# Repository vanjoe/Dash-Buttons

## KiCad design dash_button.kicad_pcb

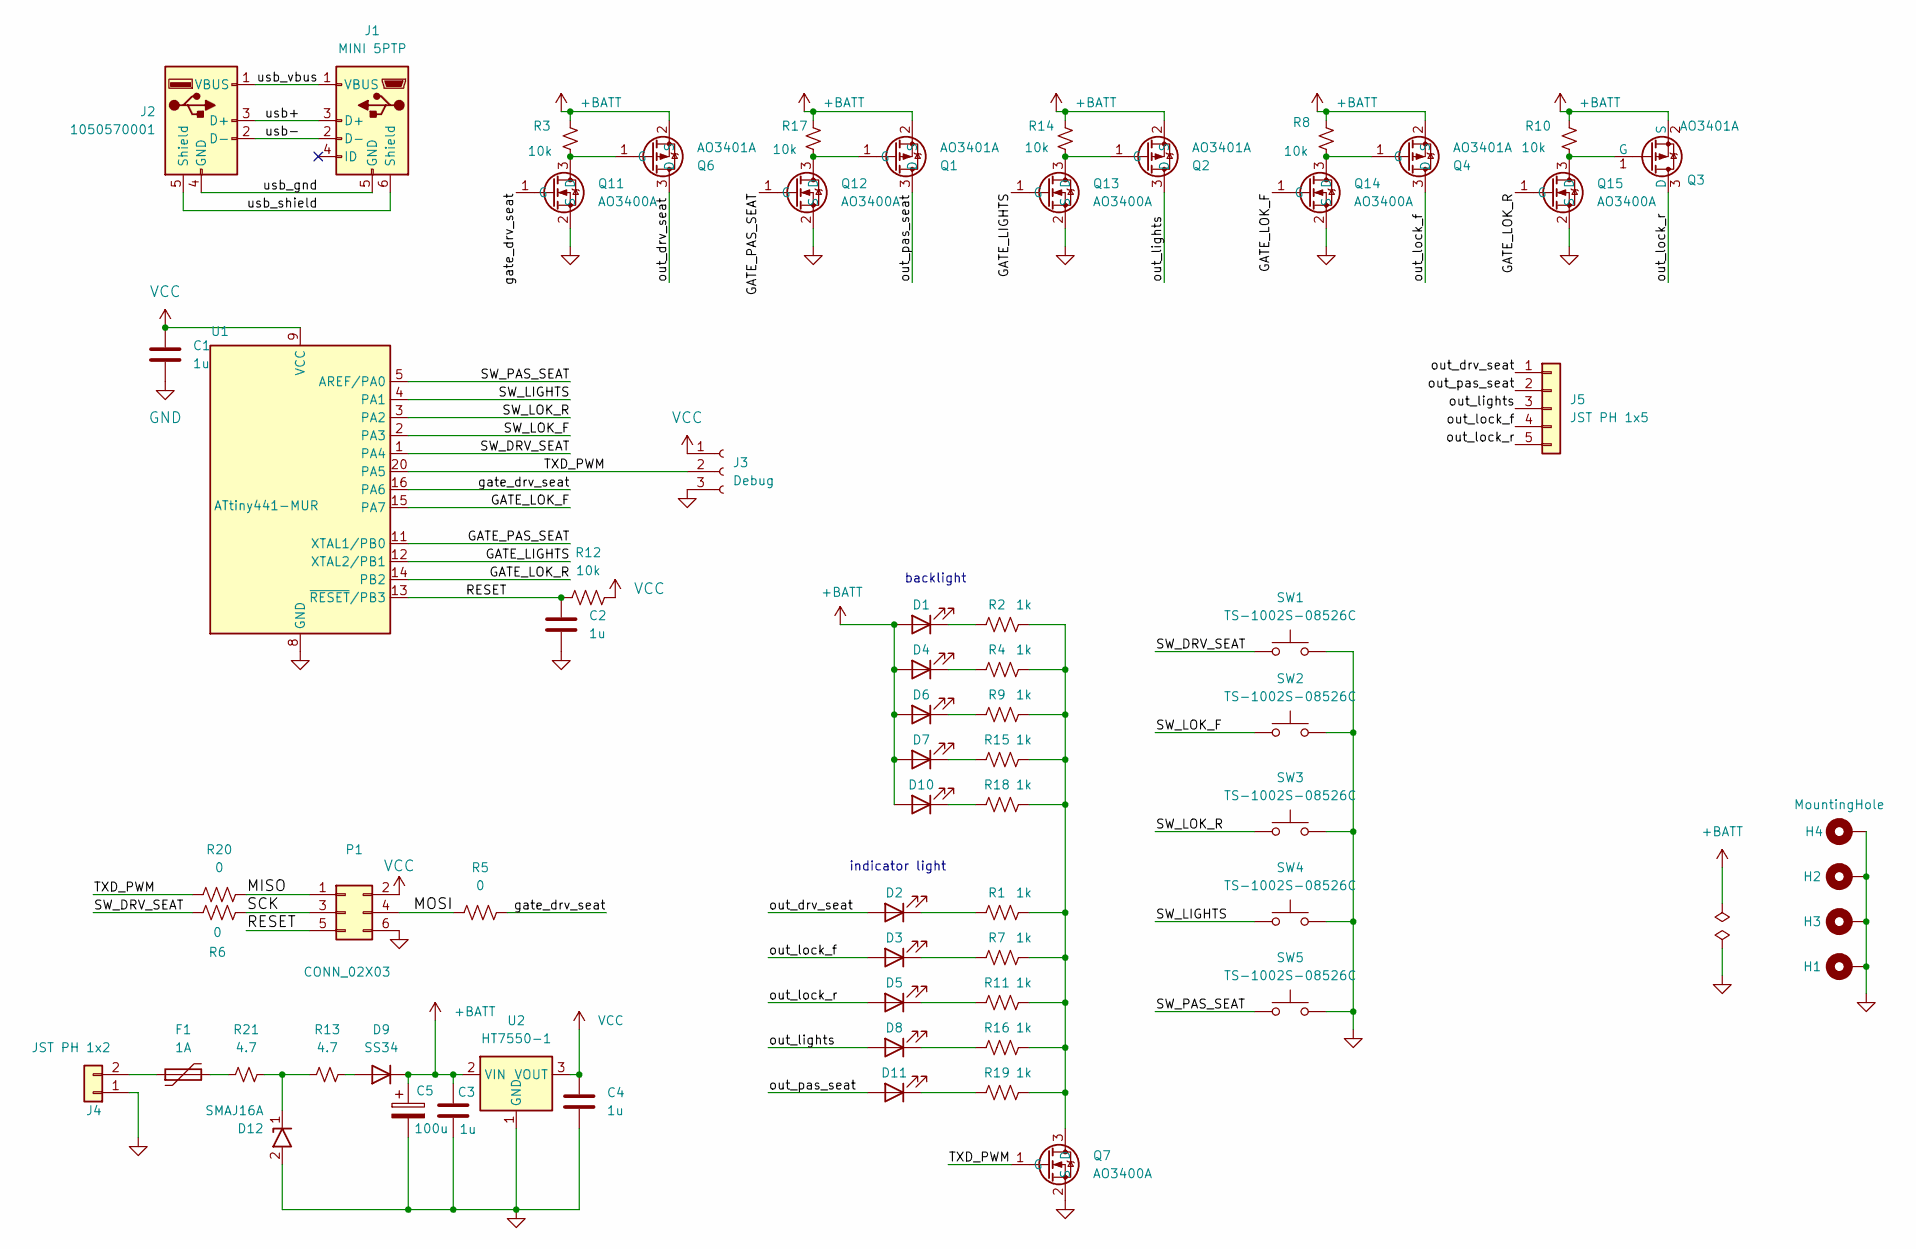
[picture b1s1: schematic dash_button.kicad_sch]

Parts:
C1, C2, C3, C4: 1u; C_0603_1608Metric; PartNo CL10A105KB8NNNC; LCSC Part # C15849
C5: 100u; CP_Elec_6.3x5.3; MPN VES101M1CTR-0605; LCSC Part # C176674
D1, D4, D6, D7, D10: KT-0805G; LED_0805_2012Metric; MPN KT-0805G; LCSC Part # C2297
D2, D3, D5, D8, D11: LED; LED_D3.0mm; MPN L314HD
D9: SS34; D_SMA; MPN SS34; LCSC Part # C8678
D12: SMAJ16A; D_SMA; MPN SMAJ16A; LCSC Part # C908770
F1: 1A; Fuse_1206_3216Metric; MPN BSMD1206-100-30V; LCSC Part # C5358568
H1, H2, H3, H4: MountingHole; MountingHole_3.2mm_M3_DIN965_Pad
J1: MINI 5PTP; USB_Mini-B_Wuerth_65100516121_Horizontal; MPN MINI 5PTP; LCSC Part # C2681563
J2: 1050570001; USB_A_Molex_105057_Vertical; MPN 1050570001; LCSC Part # C586225
J3: Debug; PinHeader_1x03_P2.54mm_Horizontal; MPN ZX-PZ2.54-1-3PWZ; LCSC Part # C7501291
J4: JST PH 1x2; JST_PH_S2B-PH-K_1x02_P2.00mm_Horizontal
J5: JST PH 1x5; JST_PH_S5B-PH-K_1x05_P2.00mm_Horizontal
P1: CONN_02X03; PinHeader_2x03_P2.54mm_Vertical; MPN ZX-PZ2.54-2-3PZZ
Q1, Q2, Q3, Q4, Q6: AO3401A; SOT-23; MPN AO3401A; LCSC Part # C15127
Q7, Q11, Q12, Q13, Q14, Q15: AO3400A; SOT-23; MPN AO3400A; LCSC Part # C20917
R1, R2, R4, R7, R9, R11, R15, R16, R18, R19: 1k; R_0805_2012Metric_Pad1.20x1.40mm_HandSolder; MPN 0805W8F1001T5E; LCSC Part # C17513
R3, R8, R10, R14, R17: 10k; R_0805_2012Metric_Pad1.20x1.40mm_HandSolder; MPN 0805W8F1002T5E; LCSC Part # C17414
R5, R6, R20: 0; R_0805_2012Metric_Pad1.20x1.40mm_HandSolder; MPN 0805W8F0000T5E; LCSC Part # C17477
R12: 10k; R_0805_2012Metric_Pad1.20x1.40mm_HandSolder; PartNo 0402WGF1002TCE; LCSC Part # C17414
R13, R21: 4.7; R_0805_2012Metric_Pad1.20x1.40mm_HandSolder; MPN 0805W8F470KT5E; LCSC Part # C17675
SW1, SW2, SW3, SW4, SW5: TS-1002S-08526C; SW_Push_1P1T_NO_6x6mm_H8.5mm; MPN TS-1002S-08526C; LCSC Part # C455117
U1: ATtiny441-MUR; QFN-20-1EP_4x4mm_P0.5mm_EP2.6x2.6mm; MPN ATTINY441-MUR; LCSC Part # C614155
U2: HT7550-1; SOT-89-3; PartNo HT7550-1; LCSC Part # C16106

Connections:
+BATT: C3.1, C5.1, D1.2 (A), D4.2 (A), D6.2 (A), D7.2 (A), D9.1 (K), D10.2 (A), Q1.2 (S), Q2.2 (S), Q3.2 (S), Q4.2 (S), Q6.2 (S), R3.1, R8.1, R10.1, R14.1, R17.1, U2.2 (VIN)
/GATE_LIGHTS: Q13.1 (G), U1.12 (XTAL2/PB1)
/GATE_LOK_F: Q14.1 (G), U1.15 (PA7)
/GATE_LOK_R: Q15.1 (G), U1.14 (PB2)
/GATE_PAS_SEAT: Q12.1 (G), U1.11 (XTAL1/PB0)
/MISO: P1.1, R20.1
/MOSI: P1.4, R5.1
/RESET: C2.1, P1.5, R12.1, U1.13 (~RESET/PB3)
/SCK: P1.3, R6.2
/SW_DRV_SEAT: R6.1, SW1.1, U1.1 (PA4)
/SW_LIGHTS: SW4.1, U1.4 (PA1)
/SW_LOK_F: SW2.1, U1.2 (PA3)
/SW_LOK_R: SW3.1, U1.3 (PA2)
/SW_PAS_SEAT: SW5.1, U1.5 (AREF/PA0)
/TXD_PWM: J3.2, Q7.1 (G), R20.2, U1.20 (PA5)
/gate_drv_seat: Q11.1 (G), R5.2, U1.16 (PA6)
/out_drv_seat: D2.2 (A), J5.1, Q6.3 (D)
/out_lights: D8.2 (A), J5.3, Q2.3 (D)
/out_lock_f: D3.2 (A), J5.4, Q4.3 (D)
/out_lock_r: D5.2 (A), J5.5, Q3.3 (D)
/out_pas_seat: D11.2 (A), J5.2, Q1.3 (D)
/usb+: J1.3 (D+), J2.3 (D+)
/usb-: J1.2 (D-), J2.2 (D-)
/usb_gnd: J1.5 (GND), J2.4 (GND)
/usb_shield: J1.6 (Shield), J2.5 (Shield)
/usb_vbus: J1.1 (VBUS), J2.1 (VBUS)
GND: C1.2, C2.2, C3.2, C4.2, C5.2, D12.2 (A2), H1.1, H2.1, H3.1, H4.1, J3.3, J4.1, P1.6, Q7.2 (S), Q11.2 (S), Q12.2 (S), Q13.2 (S), Q14.2 (S), Q15.2 (S), SW1.2, SW2.2, SW3.2, SW4.2, SW5.2, U1.8 (GND), U1.21 (GND), U2.1 (GND)
unnamed: D1.1 (K), R2.1
unnamed: D2.1 (K), R1.1
unnamed: D3.1 (K), R7.1
unnamed: D4.1 (K), R4.1
unnamed: D5.1 (K), R11.1
unnamed: D6.1 (K), R9.1
unnamed: D7.1 (K), R15.1
unnamed: D8.1 (K), R16.1
unnamed: D9.2 (A), R13.2
unnamed: D10.1 (K), R18.1
unnamed: D11.1 (K), R19.1
unnamed: D12.1 (A1), R13.1, R21.2
unnamed: F1.2, R21.1
unnamed: F1.1, J4.2
unnamed: Q1.1 (G), Q12.3 (D), R17.2
unnamed: Q7.3 (D), R1.2, R2.2, R4.2, R7.2, R9.2, R11.2, R15.2, R16.2, R18.2, R19.2
unnamed: Q6.1 (G), Q11.3 (D), R3.2
unnamed: Q2.1 (G), Q13.3 (D), R14.2
unnamed: Q4.1 (G), Q14.3 (D), R8.2
unnamed: Q3.1 (G), Q15.3 (D), R10.2
VCC: C1.1, C4.1, J3.1, P1.2, R12.2, U1.9 (VCC), U2.3 (VOUT)

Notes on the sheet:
indicator light
backlight

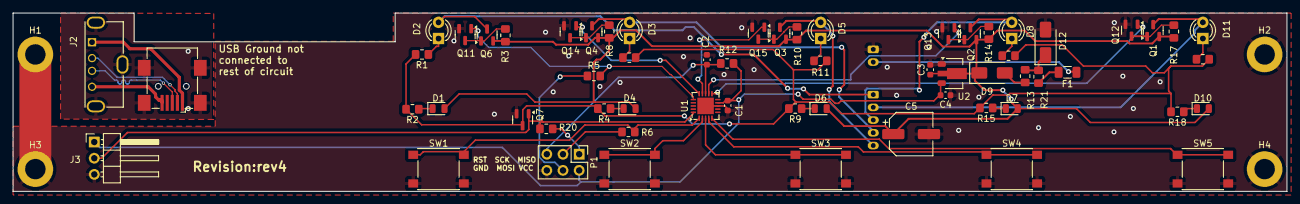
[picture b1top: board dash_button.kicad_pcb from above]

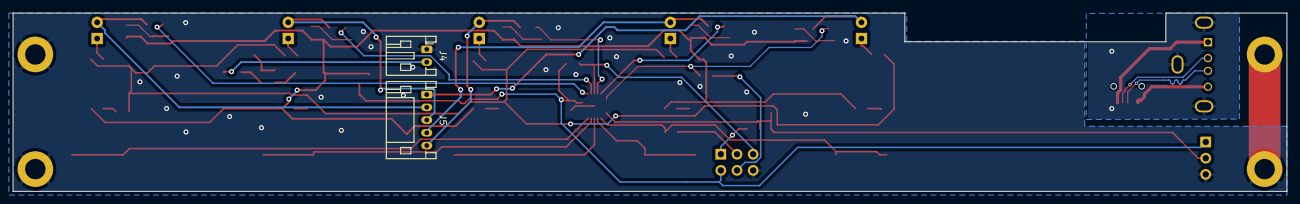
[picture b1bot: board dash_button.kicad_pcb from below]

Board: 2 copper layers, 200.0 x 28.0 mm, 67 parts (2 on the bottom side), 48 nets.

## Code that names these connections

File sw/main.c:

#include <inttypes.h>
#include <avr/io.h>
#include <util/delay.h>
#include <avr/interrupt.h>
#include <avr/eeprom.h>
//#include <avr/wdt.h>
#include <avr/sleep.h>
#include "uart.h"
#include "stdlib.h"

//currently changes target timing and serial reports
//#define dg_printf(...) do{uartEnable(); _delay_ms(100);printf(__VA_ARGS__ ); _delay_ms(100);uartDisable();}while(0);
#define dg_printf(...)
#define debugx(x) dg_printf(#x "=0x%x\r\n",(unsigned int)(x));
#define debug(x) dg_printf(#x "=%d\r\n",(unsigned int)(x));




#define wdt_reset() __asm__ __volatile__ ("wdr")
inline static __attribute__((always_inline)) void wdt_disable() {
    MCUSR = 0;
    CCP = 0xD8;
    WDTCSR = 0;
    wdt_reset();
}


#define DEBOUNCE_MS 100

#define SW_PAS_SEAT PA0
#define SW_LIGHTS   PA1
#define SW_LOCK_R   PA2
#define SW_LOCK_F   PA3
#define SW_DRV_SEAT PA4
#define BACKLIGHT_EN PA5
#define OUT_DRV_SEAT PA6
#define OUT_LOCK_F   PA7

#define OUT_PAS_SEAT PB0
#define OUT_LIGHTS   PB1
#define OUT_LOCK_R   PB2

void setup_pins(){
    PUEA = _BV(SW_DRV_SEAT) | _BV(SW_PAS_SEAT) | _BV(SW_LIGHTS) | _BV(SW_LOCK_F) | _BV(SW_LOCK_R);
    PUEB = 0;

    PORTA = _BV(BACKLIGHT_EN) | _BV(OUT_DRV_SEAT) | _BV(OUT_LOCK_F);
    PORTB = _BV(OUT_PAS_SEAT) | _BV(OUT_LIGHTS) | _BV(OUT_LOCK_R);
    DDRA = _BV(BACKLIGHT_EN) | _BV(OUT_DRV_SEAT) | _BV(OUT_LOCK_F);
    DDRB = _BV(OUT_PAS_SEAT) | _BV(OUT_LIGHTS) | _BV(OUT_LOCK_R);

}
typedef union{
 struct {
    uint8_t drv_seat ;
    uint8_t pas_seat ;
    uint8_t lights;
    uint8_t lock_f;
    uint8_t lock_r;
 };
 uint8_t as_array[5];
}switches_t;

switches_t get_sw(){
    switches_t ret;
    ret.drv_seat = !!(PINA & _BV(SW_DRV_SEAT));
    ret.pas_seat = !!(PINA & _BV(SW_PAS_SEAT));
    ret.lights   = !!(PINA & _BV(SW_LIGHTS));
    ret.lock_f   = !!(PINA & _BV(SW_LOCK_F));
    ret.lock_r   = !!(PINA & _BV(SW_LOCK_R));
    return ret;
}

void set_outputs(switches_t state){

    PORTA = ( state.drv_seat << OUT_DRV_SEAT) | (state.lock_f << OUT_LOCK_F)| _BV(BACKLIGHT_EN);
    PORTB = ( state.lights << OUT_LIGHTS) | (state.pas_seat << OUT_PAS_SEAT)| (state.lock_r << OUT_LOCK_R) ;

}
void delay_us(int us){

}
void pwm_delayms(int ms,int dutycycle){
    static const int loops_per_ms=10;
    if(dutycycle>100)dutycycle=100;
    int inv_duty=100-dutycycle;
    for(int m =0;m<ms;++m){
	//debug(m);
	for(int i=0;i<loops_per_ms;++i){
	    //debug(i);
	    PORTA|=_BV(BACKLIGHT_EN);
	    for(int d=0;d<dutycycle;++d)_delay_us(1);
            PORTA &= ~_BV(BACKLIGHT_EN);
	    for(int d=0;d<inv_duty;++d)_delay_us(1);
	}
    }
}
int set_backlight(int en){
    if(en){
	PORTA|=_BV(BACKLIGHT_EN);
    }else{
	PORTA &= ~_BV(BACKLIGHT_EN);
    }
}
void blink_slow(int blinks){
    while(blinks--){
	set_backlight(0);
	_delay_ms(500);
	set_backlight(1);
	_delay_ms(500);
    }
}
void blink_fast(int blinks){
    while(blinks--){
	set_backlight(0);
	_delay_ms(100);
	set_backlight(1);
	_delay_ms(100);
    }
}

void pwm_test(){
    int pwm = 10;
    int test=1000;
    while(--test){
	//dg_printf("pwm = %d\r\n",pwm);
	pwm_delayms(1000,pwm);
	pwm+=10;
	if (pwm > 100){
	    pwm = 00;
	}
    }
    while(1){
	dg_printf("done_test\n");
	_delay_ms(1000);
    }
}
#define DEBOUNCE_COUNT 255

void debounce_falling(uint8_t* debounce,uint8_t sw){
    if(sw) {
	*debounce = DEBOUNCE_COUNT;
    } else if(*debounce){
	*debounce = *debounce-1;
    }
}
int main (void) {
// MAIN STARTUP CODE:

    wdt_disable();
    sei();

    setup_pins();

    switches_t state = {0};
    set_outputs(state);
    switches_t last_debounce_count={0};
    switches_t debounce_count = {0};

    //pwm_test();
    //blink_slow(4);
    blink_fast(4);

    while (1) {
	switches_t sw= get_sw();

	for(int s=0;s<sizeof(sw.as_array);++s){
	    //debounce look for falling edges
	    debounce_falling(&debounce_count.as_array[s], sw.as_array[s]);
	    if(debounce_count.as_array[s] == 0 && last_debounce_count.as_array[s] == 1){
		state.as_array[s] = !state.as_array[s];
	    }
	}
	last_debounce_count = debounce_count;
	set_outputs(state);

    }
    return 0;
}

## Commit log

2024-05-27 add software files
2024-06-01 add automation for generating board_files
2024-06-01 add more stuff to build files.py
2024-06-01 update gitignore
2024-06-11 modify port definitions for sw
2024-06-11 pwm test seems to work
2024-06-11 use nchannel mosfet + pchannel mosfet
2024-07-10 Move JST connectors to center
2024-07-11 fixup BOM
2024-07-11 build_files.py generates for pcbway
2024-07-11 fix build_files.py manufacturer
2024-07-23 Change Attiny part number to attiny441-mur
2024-10-26 software mostly works except for debouncing
2024-10-28 debounce sw works
2024-10-28 flip around TVS Diode
2024-10-28 tag revision 4
